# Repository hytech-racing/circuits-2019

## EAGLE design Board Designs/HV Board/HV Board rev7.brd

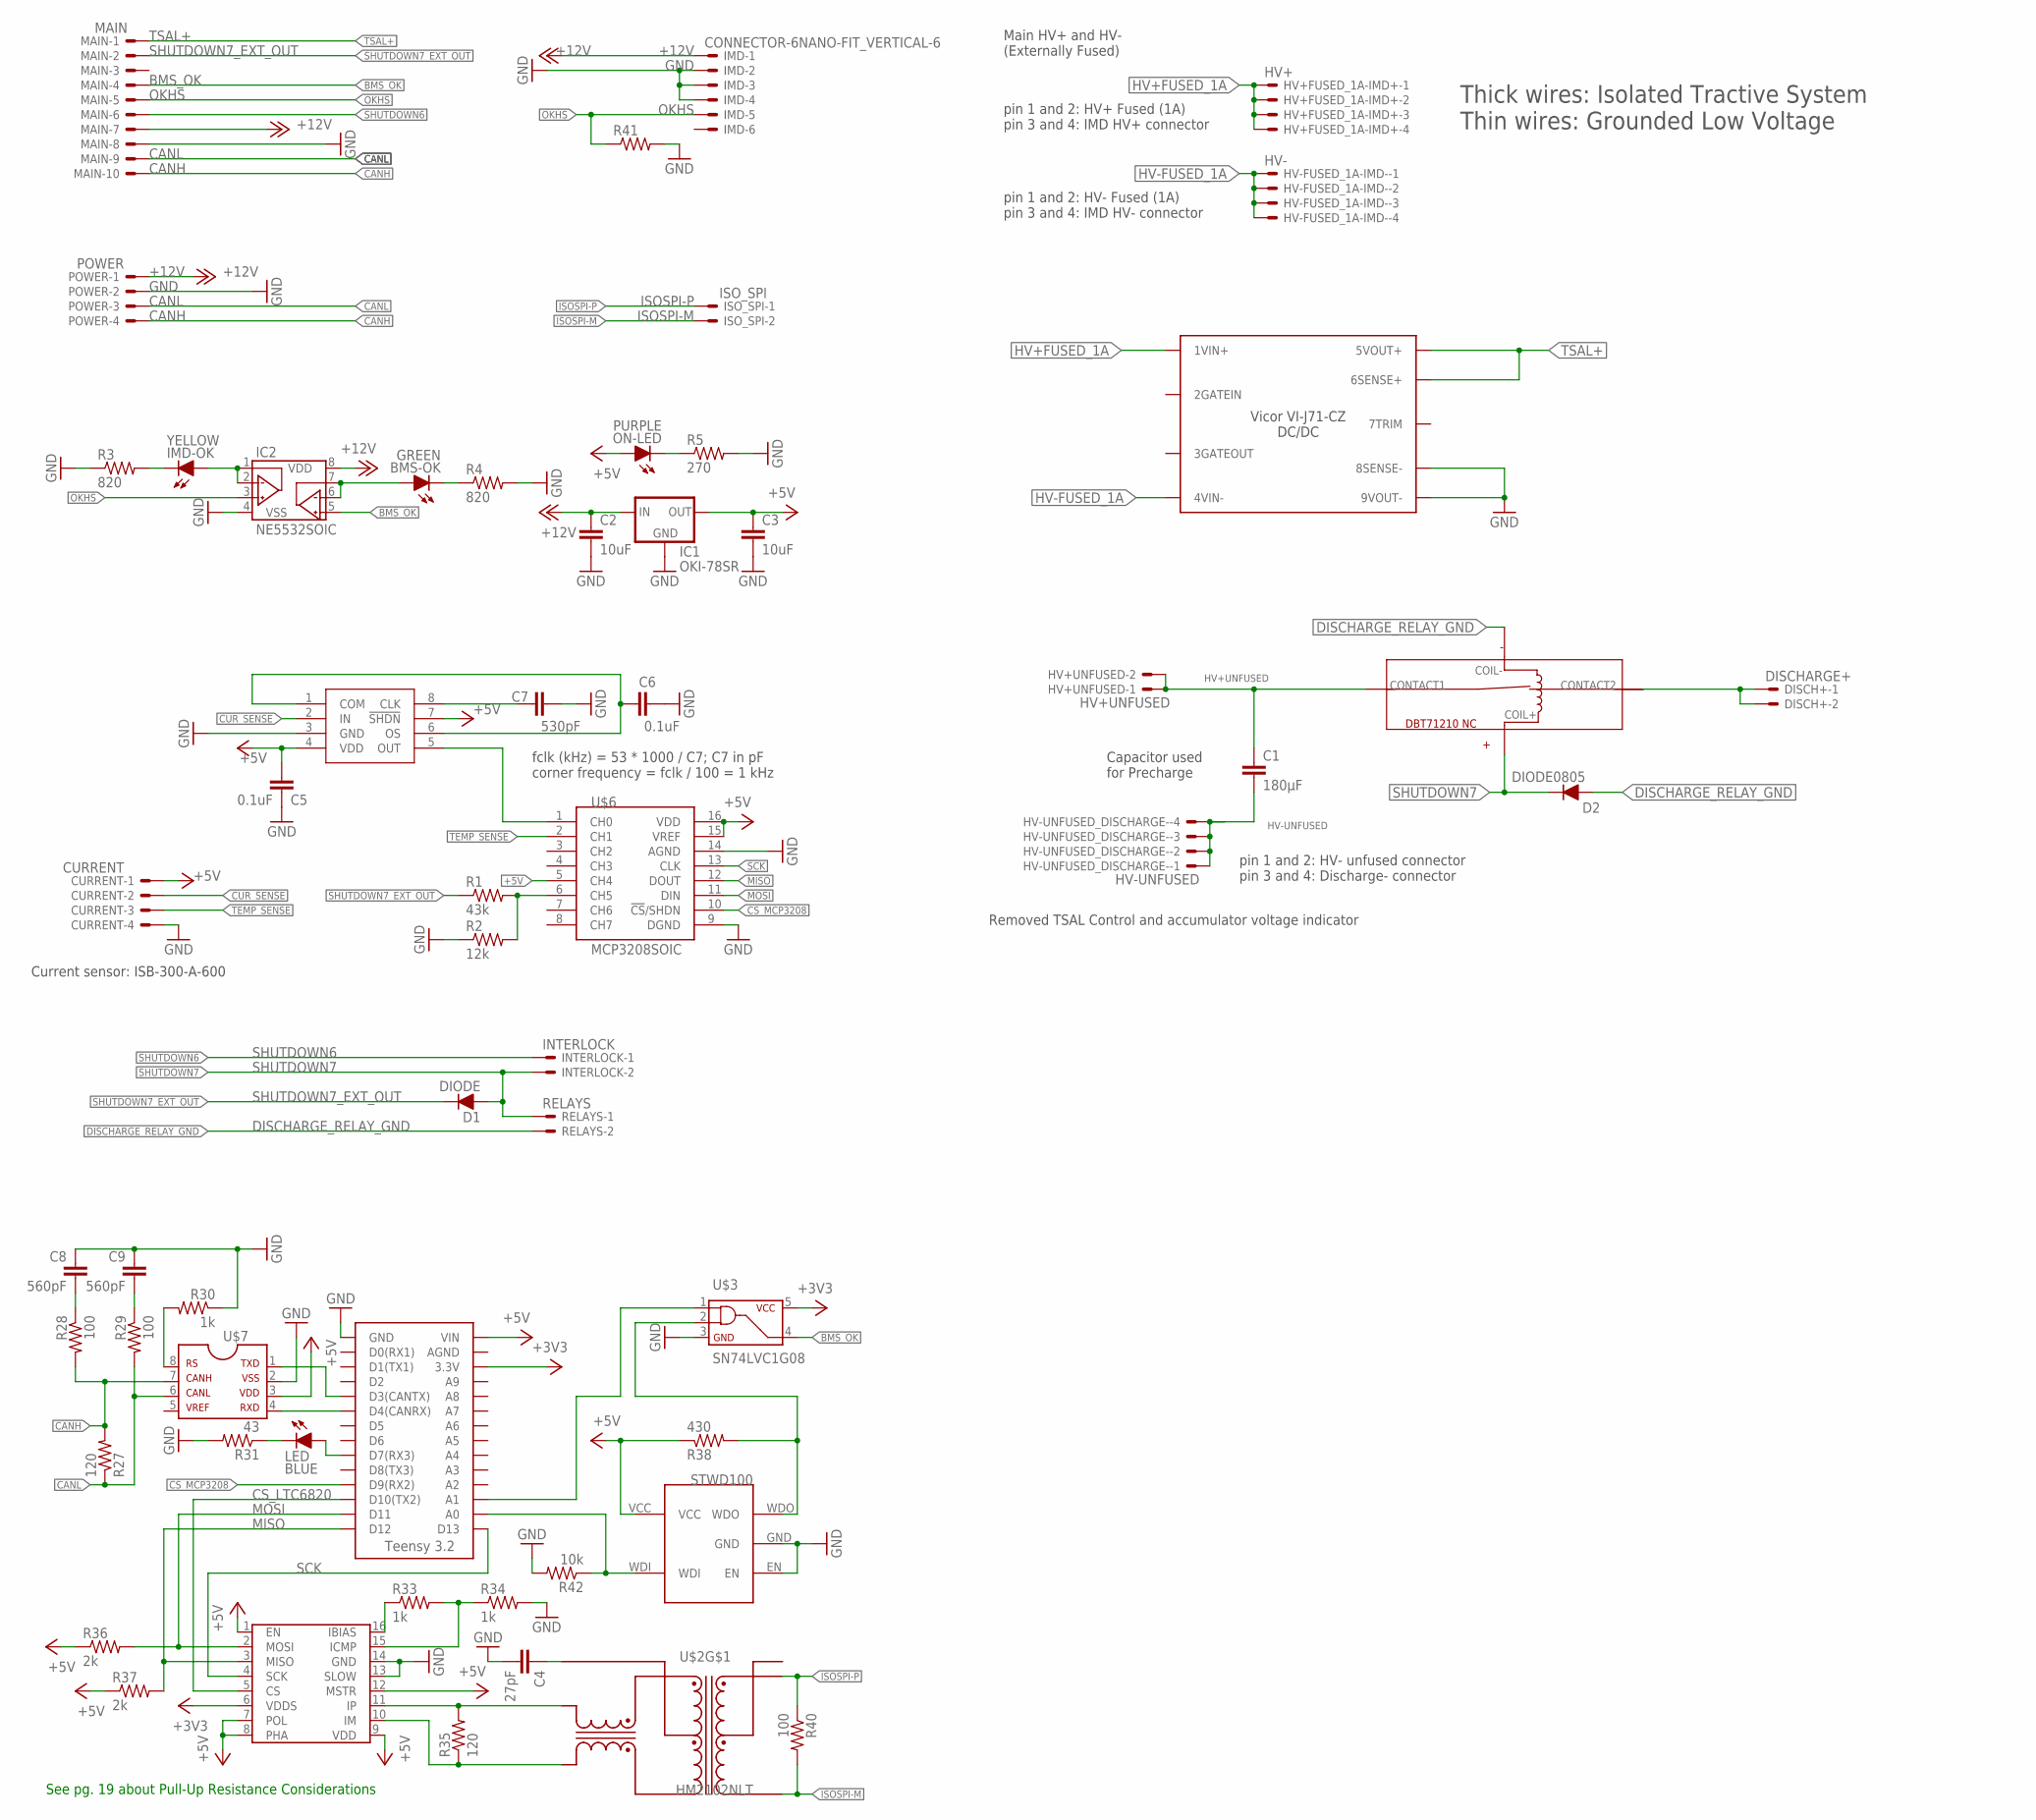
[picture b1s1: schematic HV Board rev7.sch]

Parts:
BMS-OK: GREEN; LED-805
C1: 180µF; LLS2V221MELZ
C2, C3: 10uF; 0805
C4: 27pF; 0805
C5, C6: 0.1uF; 0805
C7: 530pF; 0805
C8, C9: 560pF; 0805
CURRENT: CURRENT; NANO-FIT_VERTICAL-4
D1: DIODE; DO-41
D2: DIODE0805; 0805_D
DISCH+: DISCHARGE+; NANO-FIT_VERTICAL-2
HV+FUSED_1A-IMD+: HV+; NANO-FIT_VERTICAL-4
HV+UNFUSED: HV+UNFUSED; NANO-FIT_VERTICAL-2
HV-FUSED_1A-IMD-: HV-; NANO-FIT_VERTICAL-4
HV-UNFUSED_DISCHARGE-: HV-UNFUSED; NANO-FIT_VERTICAL-4
IC1: OKI-78SR
IC2: NE5532SOIC; SOIC-08
IMD: CONNECTOR-6NANO-FIT_VERTICAL-6; NANO-FIT_VERTICAL-6
IMD-OK: YELLOW; LED-805
INTERLOCK: INTERLOCK; NANO-FIT_VERTICAL-2
ISO_SPI: ISO_SPI; NANO-FIT_VERTICAL-2
LED: BLUE; LED-805
MAIN: MAIN; NANO-FIT_VERTICAL-10
ON-LED: PURPLE; LED-805
POWER: POWER; NANO-FIT_VERTICAL-4
R1: 43k; 0805
R2: 12k; 0805
R3, R4: 820; 0805
R5: 270; 0805
R27, R35: 120; 0805
R28, R29, R40: 100; 0805
R30, R33, R34: 1k; 0805
R31: 43; 0805
R36, R37, R41: 2k; 0805
R38: 430; 0805
R42: 10k; 0805
RELAYS: RELAYS; NANO-FIT_VERTICAL-2
U$1: MAX7480; SOIC-08
U$2: HM2102NLT
U$3: SN74LVC1G08; SOT-23-5
U$4: DBT71210
U$5: HV_DCDC_VI-J71-CZ
U$6: MCP3208SOIC; SOIC-16
U$7: MCP2551; SOIC-08
U$8: LTC6820; MSOP-16
U$9: TEENSY_3.2_SIMPLE
U$10: STWD100; SOT23-5

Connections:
+3V3: U$3.5, U$8.6 (VDDS), U$9.3.3V
+5V: C3.1, C5.1, CURRENT.P$1, IC1.3 (OUT), ON-LED.A, R36.1, R37.1, R38.1, U$1.4 (VDD), U$1.7 (!SHDN), U$6.5 (CH4), U$6.15 (VREF), U$6.16 (VDD), U$7.3, U$8.1 (EN), U$8.7 (POL), U$8.8 (PHA), U$8.9 (VDD), U$8.12 (MSTR), U$9.VIN, U$10.VCC
+12V: C2.1, IC1.1 (IN), IC2.8 (VDD), IMD.P$1, MAIN.P$7, POWER.P$1
BMS_OK: IC2.5 (VINB+), MAIN.P$4, U$3.4
CANH: MAIN.P$10, POWER.P$4, R27.2, R28.2, U$7.7
CANL: MAIN.P$9, POWER.P$3, R27.1, R29.2, U$7.6
CS_LTC6820: U$8.5 (CS), U$9.D10(TX2)
CS_MCP3208: U$6.10 (!CS!/SHDN), U$9.D9(RX2)
CUR_SENSE: CURRENT.P$2, U$1.2 (IN)
DISCHARGE_RELAY_GND: D2.A, RELAYS.P$2, U$4.COIL-
GND: C2.2, C3.2, C4.2, C5.2, C6.2, C7.2, C8.1, C9.1, CURRENT.P$4, IC1.2 (GND), IC2.4 (VSS), IMD.P$2, IMD.P$3, IMD.P$4, MAIN.P$8, POWER.P$2, R2.1, R3.1, R4.2, R5.2, R30.1, R31.2, R34.2, R41.2, R42.2, U$1.3 (GND), U$3.3, U$5.8SENSE-, U$5.9VOUT-, U$6.9 (DGND), U$6.14 (AGND), U$7.2, U$8.13 (SLOW), U$8.14 (GND), U$9.GND, U$10.EN, U$10.GND
HV+FUSED_1A: HV+FUSED_1A-IMD+.P$1, HV+FUSED_1A-IMD+.P$2, HV+FUSED_1A-IMD+.P$3, HV+FUSED_1A-IMD+.P$4, U$5.1VIN+
HV+UNFUSED: C1.P$1 (1), HV+UNFUSED.P$1, HV+UNFUSED.P$2, U$4.CONTACT1
HV+UNFUSED_FSAE_DISCHARGE: DISCH+.P$1, DISCH+.P$2, U$4.CONTACT2
HV-FUSED_1A: HV-FUSED_1A-IMD-.P$1, HV-FUSED_1A-IMD-.P$2, HV-FUSED_1A-IMD-.P$3, HV-FUSED_1A-IMD-.P$4, U$5.4VIN-
HV-UNFUSED: C1.P$2 (2), HV-UNFUSED_DISCHARGE-.P$1, HV-UNFUSED_DISCHARGE-.P$2, HV-UNFUSED_DISCHARGE-.P$3, HV-UNFUSED_DISCHARGE-.P$4
IM: R35.1, U$2.P$10 (TD-), U$8.10 (IM)
IP: R35.2, U$2.P$12 (TD+), U$8.11 (IP)
ISOSPI-M: ISO_SPI.P$2, R40.2, U$2.P$3 (MX-)
ISOSPI-P: ISO_SPI.P$1, R40.1, U$2.P$1 (MX+)
MISO: R37.2, U$6.12 (DOUT), U$8.3 (MISO), U$9.D12
MOSI: R36.2, U$6.11 (DIN), U$8.2 (MOSI), U$9.D11
unnamed: U$1.5 (OUT), U$6.1 (CH0)
unnamed: C6.1, U$1.1 (COM), U$1.6 (OS)
unnamed: ON-LED.C, R5.1
unnamed: C7.1, U$1.8 (CLK)
unnamed: R1.2, R2.2, U$6.6 (CH5)
unnamed: U$7.1, U$9.D3(CANTX)
unnamed: R30.2, U$7.8
unnamed: C8.2, R28.1
unnamed: C9.2, R29.1
unnamed: LED.C, R31.1
unnamed: R33.1, U$8.16 (IBIAS)
unnamed: R33.2, R34.1, U$8.15 (ICMP)
unnamed: C4.1, U$2.P$11 (TCT)
unnamed: U$7.4, U$9.D4(CANRX)
unnamed: LED.A, U$9.D7(RX3)
unnamed: R38.2, U$3.2, U$10.WDO
unnamed: U$3.1, U$9.A1
unnamed: IC2.1 (VOUTA), IC2.2 (VINA-), IMD-OK.A
unnamed: BMS-OK.A, IC2.6 (VINB-), IC2.7 (VOUTB)
unnamed: BMS-OK.C, R4.1
unnamed: IMD-OK.C, R3.2
unnamed: R42.1, U$9.A0, U$10.WDI
OKHS: IC2.3 (VINA+), IMD.P$5, MAIN.P$5, R41.1
SCK: U$6.13 (CLK), U$8.4 (SCK), U$9.D13
SHUTDOWN6: INTERLOCK.P$1, MAIN.P$6
SHUTDOWN7: D1.A, D2.C, INTERLOCK.P$2, RELAYS.P$1, U$4.COIL+
SHUTDOWN7_EXT_OUT: D1.C, MAIN.P$2, R1.1
TEMP_SENSE: CURRENT.P$3, U$6.2 (CH1)
TSAL+: MAIN.P$1, U$5.5VOUT+, U$5.6SENSE+

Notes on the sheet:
Current sensor: ISB-300-A-600
Main HV+ and HV- (Externally Fused)
Thick wires: Isolated Tractive System Thin wires: Grounded Low Voltage
See pg. 19 about Pull-Up Resistance Considerations
Capacitor used for Precharge
Removed TSAL Control and accumulator voltage indicator
pin 1 and 2: HV+ Fused (1A) pin 3 and 4: IMD HV+ connector
pin 1 and 2: HV- Fused (1A) pin 3 and 4: IMD HV- connector
pin 1 and 2: HV- unfused connector pin 3 and 4: Discharge- connector
fclk (kHz) = 53 * 1000 / C7; C7 in pF corner frequency = fclk / 100 = 1 kHz

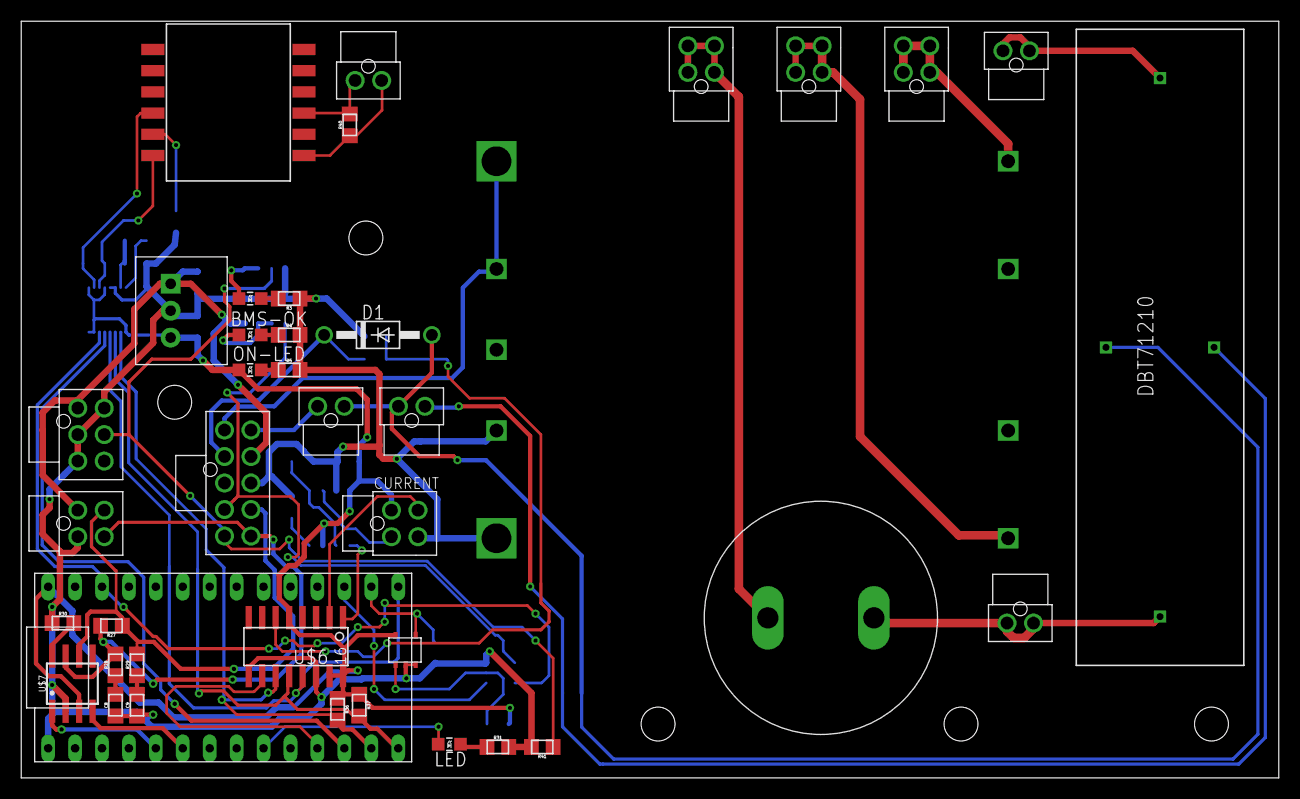
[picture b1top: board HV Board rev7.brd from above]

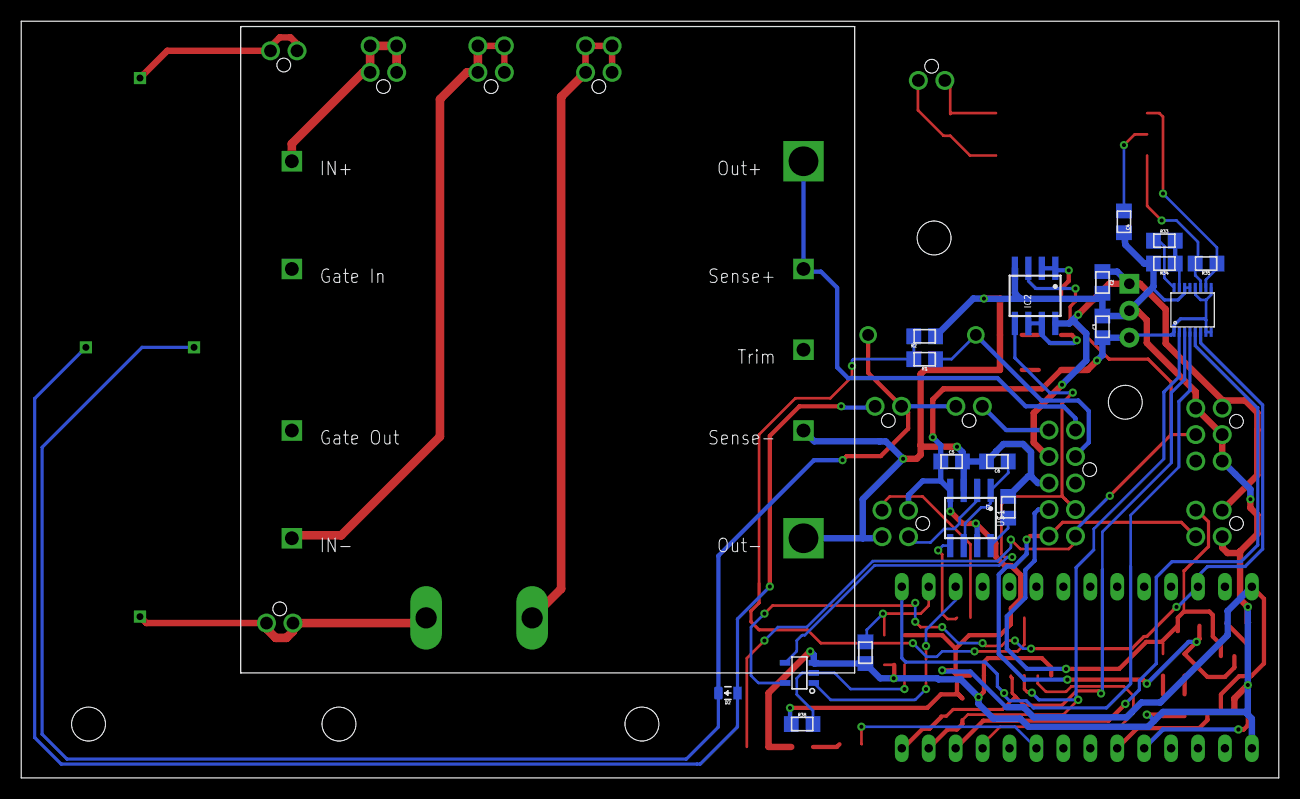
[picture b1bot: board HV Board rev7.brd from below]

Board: 2 copper layers, 118.6 x 71.4 mm, 58 parts (19 on the bottom side), 51 nets.

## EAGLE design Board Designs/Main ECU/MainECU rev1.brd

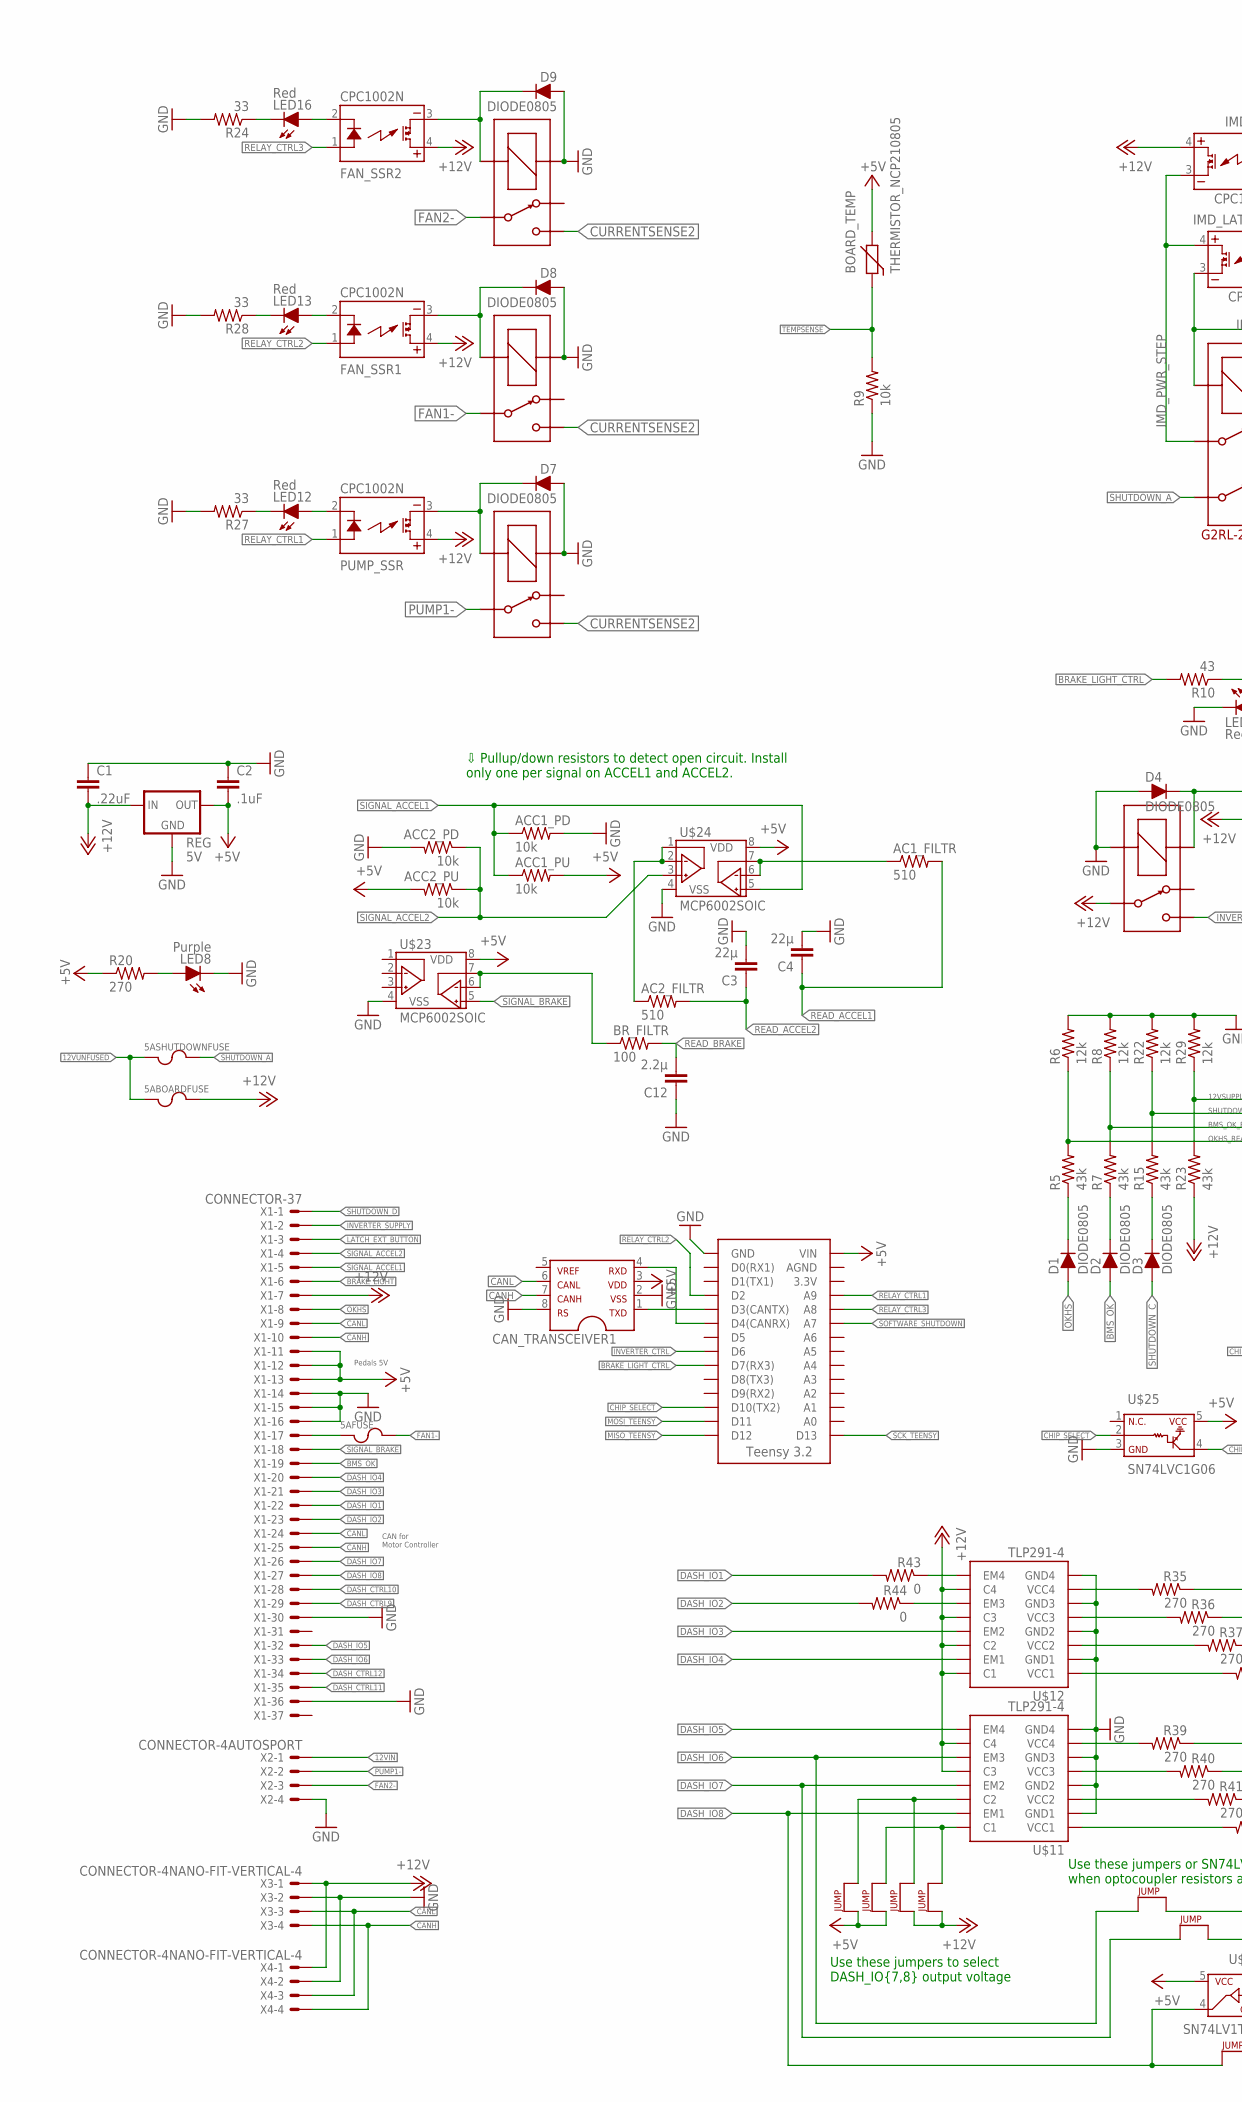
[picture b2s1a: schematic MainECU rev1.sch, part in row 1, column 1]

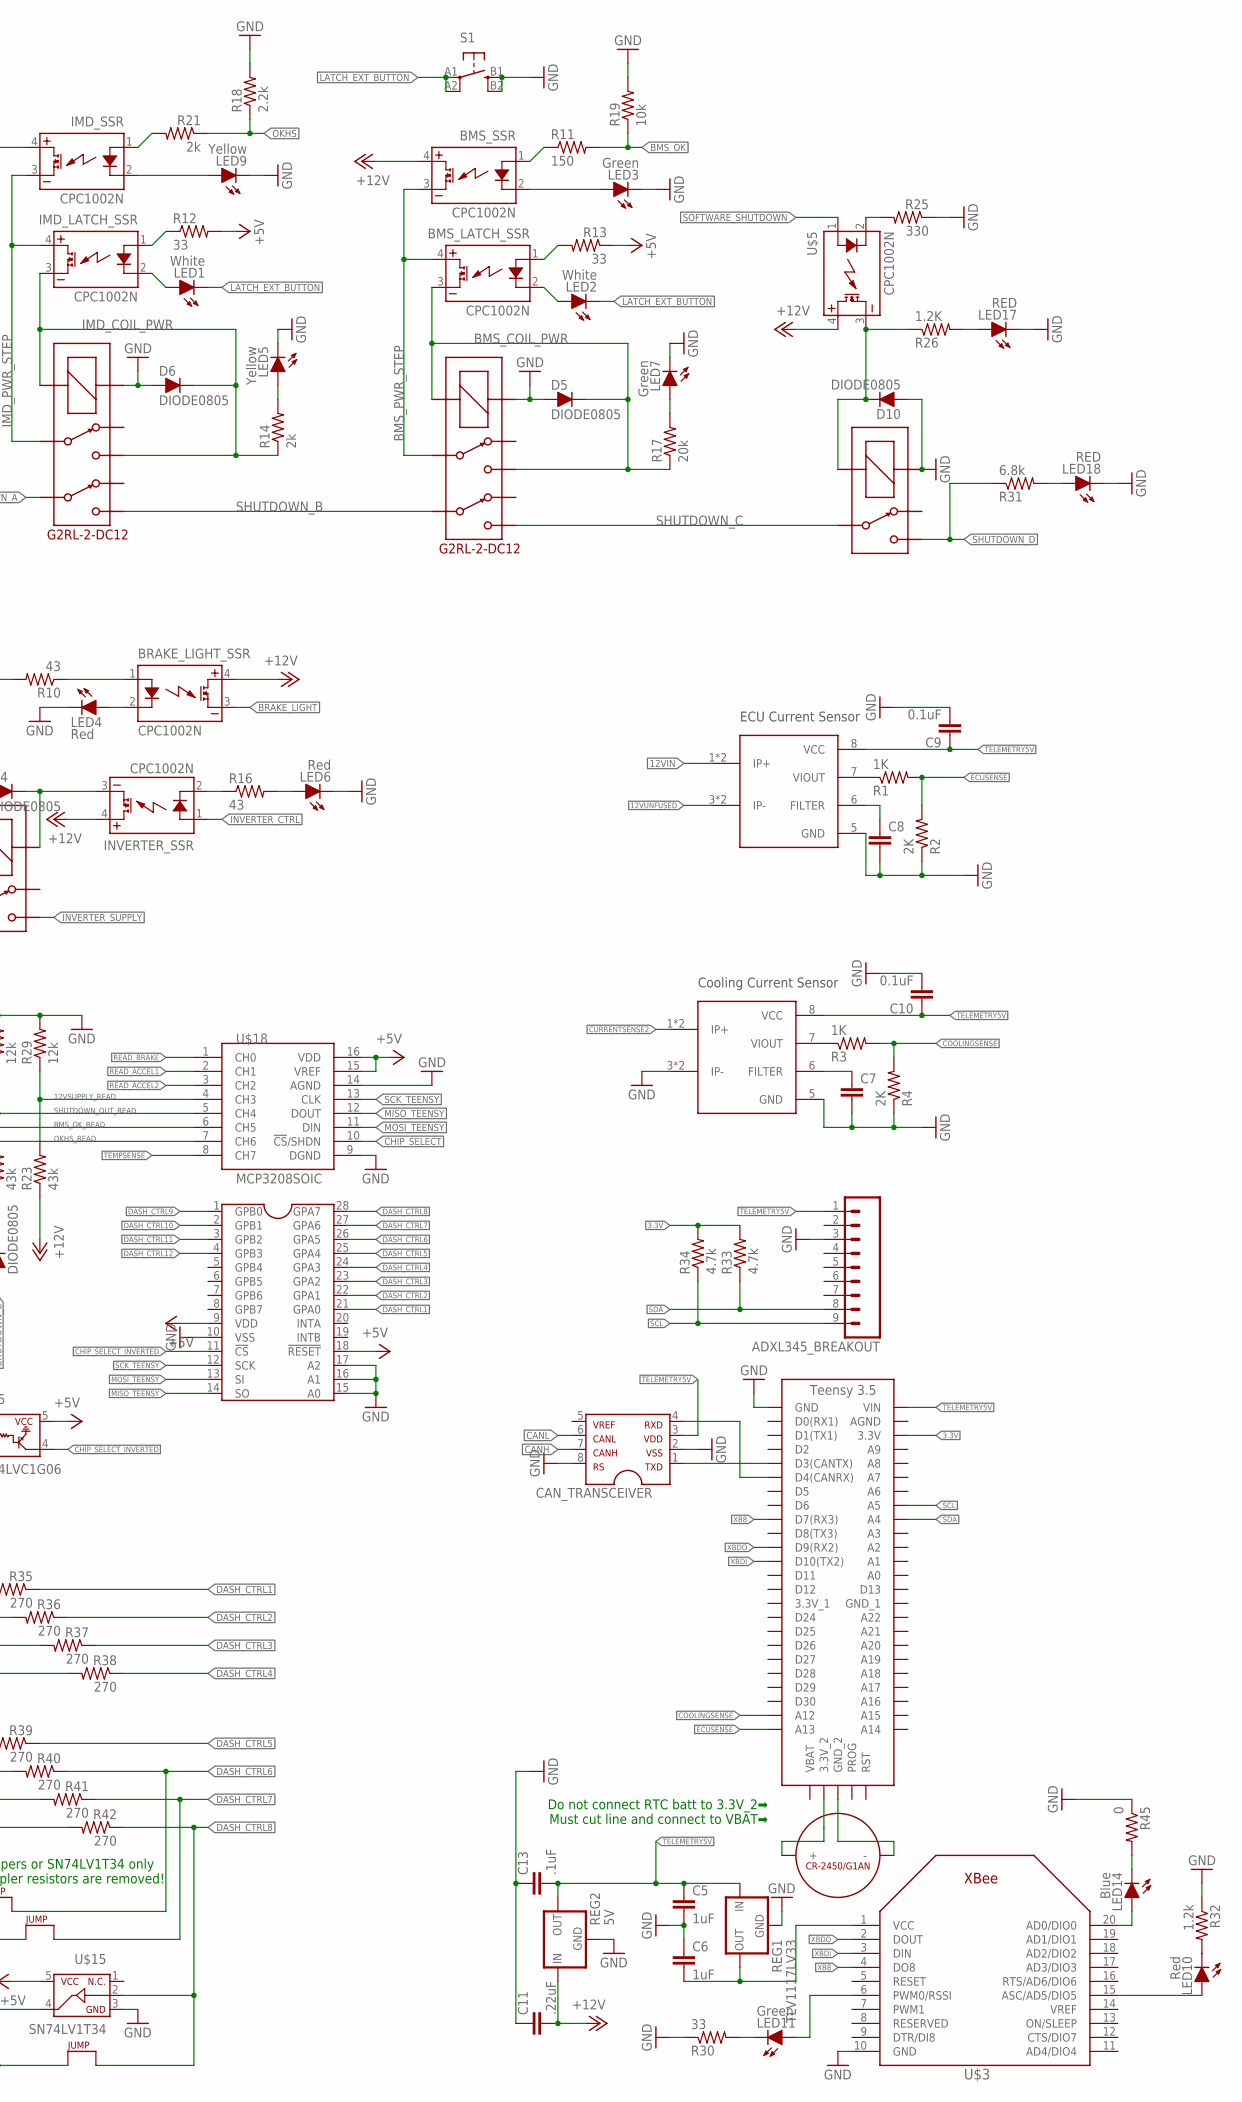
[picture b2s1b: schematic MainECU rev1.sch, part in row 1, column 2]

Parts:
5ABOARDFUSE, 5AFUSE, 5ASHUTDOWNFUSE: FUSE_MINIBLADE; MINI-BLADE_FUSE_HOLDER
AC1_FILTR, AC2_FILTR: 510; 0805
ACC1_PD, ACC1_PU, ACC2_PD, ACC2_PU: 10k; 0805
ADXL345_BREAKOUT: M09; 1X09
BMS_LATCH_SSR: CPC1002N; SOP04
BMS_SSR: CPC1002N; SOP04
BOARD_TEMP: THERMISTOR_NCP210805; 0805
BRAKE_LIGHT_SSR: CPC1002N; SOP04
BR_FILTR: 100; 0805
C1, C11: .22uF; 0805
C2, C13: .1uF; 0805
C3, C4: 22µ; 0805
C5, C6: 1uF; 0805
C7, C8: CAP0805; 0805
C9, C10: 0.1uF; 0805
C12: 2.2µ; 0805
CAN_TRANSCEIVER, CAN_TRANSCEIVER1: MCP2551; SOIC-08
D1, D2, D3, D4, D5, D6, D7, D8, D9, D10: DIODE0805; 0805_D
FAN_SSR1, FAN_SSR2: CPC1002N; SOP04
IMD_LATCH_SSR: CPC1002N; SOP04
IMD_SHUTDOWN, IMD_SHUTDOWN1: G2RL-2-DC12; G2RL-2
IMD_SSR: CPC1002N; SOP04
INVERTER_SSR: CPC1002N; SOP04
LED1, LED2: White; LED-805
LED3, LED7, LED11: Green; LED-805
LED4, LED6, LED10, LED12, LED13, LED16: Red; LED-805
LED5, LED9: Yellow; LED-805
LED8: Purple; LED-805
LED14: Blue; LED-805
LED17, LED18: RED; LED-805
PUMP_SSR: CPC1002N; SOP04
R1, R3: 1K; 0805
R2, R4: 2K; 0805
R5, R7, R15, R23: 43k; 0805
R6, R8, R22, R29: 12k; 0805
R9, R19: 10k; 0805
R10, R16: 43; 0805
R11: 150; 0805
R12, R13, R24, R27, R28, R30: 33; 0805
R14, R21: 2k; 0805
R17: 20k; 0805
R18: 2.2k; 0805
R20, R35, R36, R37, R38, R39, R40, R41, R42: 270; 0805
R25: 330; 0805
R26: 1.2K; 0805
R31: 6.8k; 0805
R32: 1.2k; 0805
R33, R34: 4.7k; 0805
R43, R44, R45: 0; 0805
REG, REG2: 5V; OKI-78SR
REG1: TLV1117LV33; SOT223
S1: BTN_10-XXSMD; TACTILE_SWITCH_SMD_6.2MM_TALL
SOFTWARE_SHUTOFF: G5LE; ZF112
U$1: TEENSY_3.2_SIMPLE
U$2: TEENSY_3.5_EXT
U$3: XBEE
U$4, U$6, U$7, U$8: G5LE; ZF112
U$5: CPC1002N; SOP04
U$9, U$10: ACS715_CURRENT_SENSOR; SOP8
U$11, U$12: TLP291-4; SOIC-16
U$13, U$14, U$16, U$19, U$20, U$21, U$22: JUMPER; 0805
U$15: SN74LV1T34; SOT-23-5
U$17: MCP23S17SSOP28; SSOP28
U$18: MCP3208SOIC; SOIC-16
U$23, U$24: MCP6002SOIC; SOIC-08
U$25: SN74LVC1G06; SOT-23-5
U$26: CR-2450/G1AN
X1: CONNECTOR-37; AUTOSPORT_14-35
X2: CONNECTOR-4AUTOSPORT; AUTOSPORT_12-04
X3, X4: CONNECTOR-4NANO-FIT-VERTICAL-4; NANO-FIT_VERTICAL-4

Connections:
3.3V: R33.2, R34.2, U$2.3.3V
12VIN: U$9.1 (IP+), U$9.2 (IP+), X2.P$1
12VSUPPLY_READ: R23.2, R29.1, U$18.4 (CH3)
12VUNFUSED: 5ABOARDFUSE.L1 (1), 5ABOARDFUSE.L2 (1), 5ASHUTDOWNFUSE.L1 (1), 5ASHUTDOWNFUSE.L2 (1), U$9.3 (IP-), U$9.4 (IP-)
+5V: ACC1_PU.2, ACC2_PU.2, BOARD_TEMP.1, C2.2, CAN_TRANSCEIVER1.3, R12.2, R13.1, R20.1, REG.3 (OUT), U$1.VIN, U$15.5, U$17.9 (VDD), U$17.18 (!RESET), U$18.15 (VREF), U$18.16 (VDD), U$20.1, U$22.1, U$23.8 (VDD), U$24.8 (VDD), U$25.5, X1.P$11, X1.P$12, X1.P$13
+12V: 5ABOARDFUSE.R1 (2), 5ABOARDFUSE.R2 (2), BMS_SSR.4 (DC+), BRAKE_LIGHT_SSR.4 (DC+), C1.2, C11.2, FAN_SSR1.4 (DC+), FAN_SSR2.4 (DC+), IMD_SSR.4 (DC+), INVERTER_SSR.4 (DC+), PUMP_SSR.4 (DC+), R23.1, REG.1 (IN), REG2.1 (IN), U$5.4 (DC+), U$8.P, U$11.10 (C4), U$11.12 (C3), U$12.10 (C4), U$12.12 (C3), U$12.14 (C2), U$12.16 (C1), U$16.1, U$21.1, X1.P$7, X3.P$1, X4.P$1
BMS_COIL_PWR: BMS_LATCH_SSR.3 (DC-), D5.C, IMD_SHUTDOWN1.4, IMD_SHUTDOWN1.COIL-, R17.1
BMS_OK: D2.A, R11.2, R19.1, X1.P$19
BMS_OK_READ: R7.2, R8.1, U$18.6 (CH5)
BMS_PWR_STEP: BMS_LATCH_SSR.4 (DC+), BMS_SSR.3 (DC-), IMD_SHUTDOWN1.3
BRAKE_LIGHT: BRAKE_LIGHT_SSR.3 (DC-), X1.P$6
BRAKE_LIGHT_CTRL: R10.2, U$1.D7(RX3)
CANH: CAN_TRANSCEIVER.7, CAN_TRANSCEIVER1.7, X1.P$10, X1.P$25, X3.P$4, X4.P$4
CANL: CAN_TRANSCEIVER.6, CAN_TRANSCEIVER1.6, X1.P$9, X1.P$24, X3.P$3, X4.P$3
CHIP_SELECT: U$1.D10(TX2), U$18.10 (!CS!/SHDN), U$25.2
CHIP_SELECT_INVERTED: U$17.11 (!CS), U$25.4
COOLINGSENSE: R3.2, R4.2, U$2.A12
CURRENTSENSE2: U$4.S, U$6.S, U$7.S, U$10.1 (IP+), U$10.2 (IP+)
DASH_CTRL1: R35.1, U$17.21 (GPA0)
DASH_CTRL2: R36.1, U$17.22 (GPA1)
DASH_CTRL3: R37.1, U$17.23 (GPA2)
DASH_CTRL4: R38.1, U$17.24 (GPA3)
DASH_CTRL5: R39.1, U$17.25 (GPA4)
DASH_CTRL6: R40.1, U$13.2, U$17.26 (GPA5)
DASH_CTRL7: R41.1, U$14.2, U$17.27 (GPA6)
DASH_CTRL8: R42.1, U$15.2, U$17.28 (GPA7), U$19.2
DASH_CTRL9: U$17.1 (GPB0), X1.P$29
DASH_CTRL10: U$17.2 (GPB1), X1.P$28
DASH_CTRL11: U$17.3 (GPB2), X1.P$35
DASH_CTRL12: U$17.4 (GPB3), X1.P$34
DASH_IO1: R43.2, X1.P$22
DASH_IO2: R44.2, X1.P$23
DASH_IO3: U$12.13 (EM2), X1.P$21
DASH_IO4: U$12.15 (EM1), X1.P$20
DASH_IO5: U$11.9 (EM4), X1.P$32
DASH_IO6: U$11.11 (EM3), U$13.1, X1.P$33
DASH_IO7: U$11.13 (EM2), U$14.1, X1.P$26
DASH_IO8: U$11.15 (EM1), U$15.4, U$19.1, X1.P$27
ECUSENSE: R1.2, R2.2, U$2.A13
FAN1-: 5AFUSE.R1 (2), 5AFUSE.R2 (2), U$7.P
FAN2-: U$4.P, X2.P$3
GND: ACC1_PD.2, ACC2_PD.2, ADXL345_BREAKOUT.3, C1.1, C2.1, C3.2, C4.2, C5.2, C6.1, C7.2, C8.2, C9.2, C10.2, C11.1, C12.1, C13.1, CAN_TRANSCEIVER.2, CAN_TRANSCEIVER.8, CAN_TRANSCEIVER1.2, CAN_TRANSCEIVER1.8, D4.A, D5.A, D6.A, D7.A, D8.A, D9.A, D10.A, IMD_SHUTDOWN.COIL+, IMD_SHUTDOWN1.COIL+, LED3.C, LED4.C, LED5.C, LED6.C, LED7.C, LED8.C, LED9.C, LED17.C, LED18.C, R2.1, R4.1, R6.2, R8.2, R9.1, R18.2, R19.2, R22.2, R24.2, R25.1, R27.2, R28.2, R29.2, R30.1, R32.1, R45.1, REG.2 (GND), REG1.1 (GND), REG2.2 (GND), S1.B1 (S), S1.B2 (S1), SOFTWARE_SHUTOFF.1 (COIL+), U$1.GND, U$2.GND, U$3.10 (GND), U$4.1 (COIL+), U$6.1 (COIL+), U$7.1 (COIL+), U$8.2 (COIL-), U$9.5 (GND), U$10.3 (IP-), U$10.4 (IP-), U$10.5 (GND), U$11.2 (GND1), U$11.4 (GND2), U$11.6 (GND3), U$11.8 (GND4), U$12.2 (GND1), U$12.4 (GND2), U$12.6 (GND3), U$12.8 (GND4), U$15.3, U$17.10 (VSS), U$17.15 (A0), U$17.16 (A1), U$17.17 (A2), U$18.9 (DGND), U$18.14 (AGND), U$23.4 (VSS), U$24.4 (VSS), U$25.3, X1.P$14, X1.P$15, X1.P$16, X1.P$30, X1.P$36, X2.P$4, X3.P$2, X4.P$2
IMD_COIL_PWR: D6.C, IMD_LATCH_SSR.3 (DC-), IMD_SHUTDOWN.4, IMD_SHUTDOWN.COIL-, R14.1
IMD_PWR_STEP: IMD_LATCH_SSR.4 (DC+), IMD_SHUTDOWN.3, IMD_SSR.3 (DC-)
INVERTER_CTRL: INVERTER_SSR.1 (CONTROL+), U$1.D6
INVERTER_SUPPLY: U$8.S, X1.P$2
LATCH_EXT_BUTTON: LED1.C, LED2.C, S1.A1, S1.A2 (P1), X1.P$3
MISO_TEENSY: U$1.D12, U$17.14 (SO), U$18.12 (DOUT)
MOSI_TEENSY: U$1.D11, U$17.13 (SI), U$18.11 (DIN)
unnamed: 5AFUSE.L1 (1), 5AFUSE.L2 (1), X1.P$17
unnamed: IMD_LATCH_SSR.2 (CONTROL-), LED1.A
unnamed: R1.1, U$9.7 (VIOUT)
unnamed: D7.C, PUMP_SSR.3 (DC-), U$6.2 (COIL-)
unnamed: IMD_LATCH_SSR.1 (CONTROL+), R12.1
unnamed: R3.1, U$10.7 (VIOUT)
unnamed: BRAKE_LIGHT_SSR.2 (CONTROL-), LED4.A
unnamed: C8.1, U$9.6 (FILTER)
unnamed: BMS_SSR.2 (CONTROL-), LED3.A
unnamed: D1.C, R5.1
unnamed: D2.C, R7.1
unnamed: BMS_LATCH_SSR.1 (CONTROL+), R13.2
unnamed: CAN_TRANSCEIVER.4, U$2.D4(CANRX)
unnamed: CAN_TRANSCEIVER.1, U$2.D3(CANTX)
unnamed: CAN_TRANSCEIVER1.4, U$1.D4(CANRX)
unnamed: BMS_LATCH_SSR.2 (CONTROL-), LED2.A
unnamed: BRAKE_LIGHT_SSR.1 (CONTROL+), R10.1
unnamed: BMS_SSR.1 (CONTROL+), R11.1
unnamed: LED5.A, R14.2
unnamed: D8.C, FAN_SSR1.3 (DC-), U$7.2 (COIL-)
unnamed: D9.C, FAN_SSR2.3 (DC-), U$4.2 (COIL-)
unnamed: CAN_TRANSCEIVER1.1, U$1.D3(CANTX)
unnamed: AC2_FILTR.1, U$24.1 (VOUTA), U$24.2 (VINA-)
unnamed: AC1_FILTR.1, U$24.6 (VINB-), U$24.7 (VOUTB)
unnamed: BR_FILTR.1, U$23.6 (VINB-), U$23.7 (VOUTB)
unnamed: D4.C, INVERTER_SSR.3 (DC-), U$8.1 (COIL+)
unnamed: INVERTER_SSR.2 (CONTROL-), R16.1
unnamed: LED6.A, R16.2
unnamed: LED8.A, R20.2
unnamed: LED16.C, R24.1
unnamed: IMD_SSR.1 (CONTROL+), R21.2
unnamed: LED7.A, R17.2
unnamed: D3.C, R15.1
unnamed: IMD_SSR.2 (CONTROL-), LED9.A
unnamed: LED14.C, R45.2
unnamed: LED13.C, R28.1
unnamed: LED12.C, R27.1
unnamed: LED12.A, PUMP_SSR.2 (CONTROL-)
unnamed: FAN_SSR2.2 (CONTROL-), LED16.A
unnamed: LED18.A, R31.2
unnamed: U$2.3.3V_2, U$26.+_0 (+), U$26.+_1 (+)
unnamed: FAN_SSR1.2 (CONTROL-), LED13.A
unnamed: D10.C, R26.1, SOFTWARE_SHUTOFF.2 (COIL-), U$5.3 (DC-)
unnamed: R25.2, U$5.2 (CONTROL-)
unnamed: LED11.C, R30.2
unnamed: LED17.A, R26.2
unnamed: LED11.A, U$3.6 (PWM0/RSSI)
unnamed: C7.1, U$10.6 (FILTER)
unnamed: LED10.A, U$3.15 (ASC/AD5/DIO5)
unnamed: LED10.C, R32.2
unnamed: R35.2, U$12.7 (VCC4)
unnamed: R36.2, U$12.5 (VCC3)
unnamed: R37.2, U$12.3 (VCC2)
unnamed: R38.2, U$12.1 (VCC1)
unnamed: R39.2, U$11.7 (VCC4)
unnamed: R40.2, U$11.5 (VCC3)
unnamed: R41.2, U$11.3 (VCC2)
unnamed: R42.2, U$11.1 (VCC1)
unnamed: R43.1, U$12.9 (EM4)
unnamed: R44.1, U$12.11 (EM3)
unnamed: U$11.16 (C1), U$16.2, U$20.2
unnamed: U$11.14 (C2), U$21.2, U$22.2
unnamed: LED14.A, U$3.20 (AD0/DIO0)
unnamed: U$2.GND_2, U$26.-
OKHS: D1.A, R18.1, R21.1, X1.P$8
OKHS_READ: R5.2, R6.1, U$18.7 (CH6)
PUMP1-: U$6.P, X2.P$2
READ_ACCEL1: AC1_FILTR.2, C4.1, U$18.2 (CH1)
READ_ACCEL2: AC2_FILTR.2, C3.1, U$18.3 (CH2)
READ_BRAKE: BR_FILTR.2, C12.2, U$18.1 (CH0)
RELAY_CTRL1: PUMP_SSR.1 (CONTROL+), U$1.A9
RELAY_CTRL2: FAN_SSR1.1 (CONTROL+), U$1.D2
RELAY_CTRL3: FAN_SSR2.1 (CONTROL+), U$1.A8
SCK_TEENSY: U$1.D13, U$17.12 (SCK), U$18.13 (CLK)
SCL: ADXL345_BREAKOUT.9, R34.1, U$2.A5
SDA: ADXL345_BREAKOUT.8, R33.1, U$2.A4
SHUTDOWN_A: 5ASHUTDOWNFUSE.R1 (2), 5ASHUTDOWNFUSE.R2 (2), IMD_SHUTDOWN.6
SHUTDOWN_B: IMD_SHUTDOWN.5, IMD_SHUTDOWN1.6
SHUTDOWN_C: D3.A, IMD_SHUTDOWN1.5, SOFTWARE_SHUTOFF.P
SHUTDOWN_D: R31.1, SOFTWARE_SHUTOFF.S, X1.P$1
SHUTDOWN_OUT_READ: R15.2, R22.1, U$18.5 (CH4)
SIGNAL_ACCEL1: ACC1_PD.1, ACC1_PU.1, U$24.5 (VINB+), X1.P$5
SIGNAL_ACCEL2: ACC2_PD.1, ACC2_PU.1, U$24.3 (VINA+), X1.P$4
SIGNAL_BRAKE: U$23.5 (VINB+), X1.P$18
SOFTWARE_SHUTDOWN: U$1.A7, U$5.1 (CONTROL+)
TELEMETRY5V: ADXL345_BREAKOUT.1, C5.1, C9.1, C10.1, C13.2, CAN_TRANSCEIVER.3, REG1.3 (IN), REG2.3 (OUT), U$2.VIN, U$9.8 (VCC), U$10.8 (VCC)
TEMPSENSE: BOARD_TEMP.2, R9.2, U$18.8 (CH7)
VCC: C6.2, REG1.2 (OUT), REG1.4 (OUT), U$3.1 (VCC)
XB8: U$2.D7(RX3), U$3.4 (DO8)
XBDI: U$2.D10(TX2), U$3.3 (DIN)
XBDO: U$2.D9(RX2), U$3.2 (DOUT)

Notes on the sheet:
ECU Current Sensor
Cooling Current Sensor
⇩ Pullup/down resistors to detect open circuit. Install only one per signal on ACCEL1 and ACCEL2.
Use these jumpers or SN74LV1T34 only when optocoupler resistors are removed!
Use these jumpers to select DASH_IO{7,8} output voltage
Pedals 5V
CAN for Motor Controller
Do not connect RTC batt to 3.3V_2➡ Must cut line and connect to VBAT➡

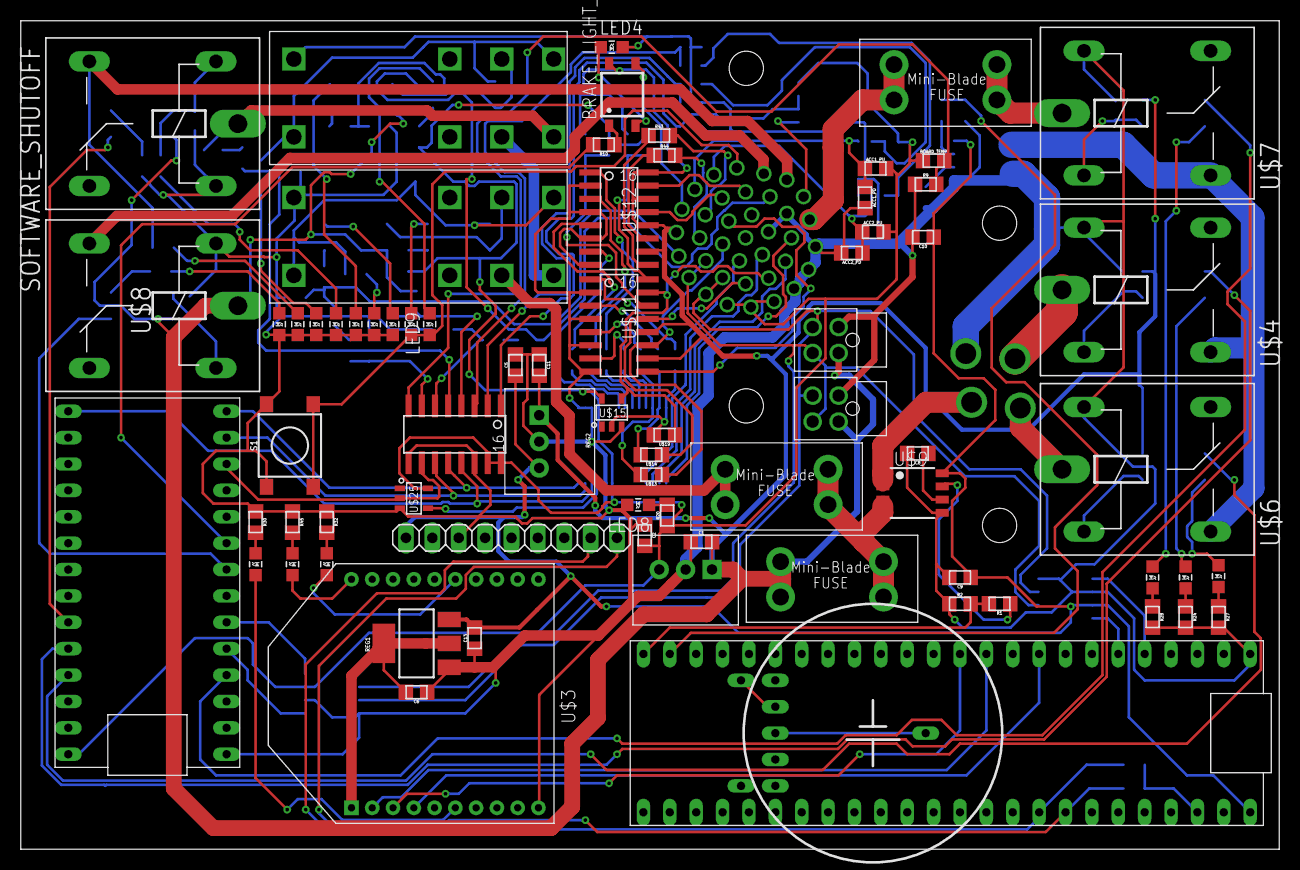
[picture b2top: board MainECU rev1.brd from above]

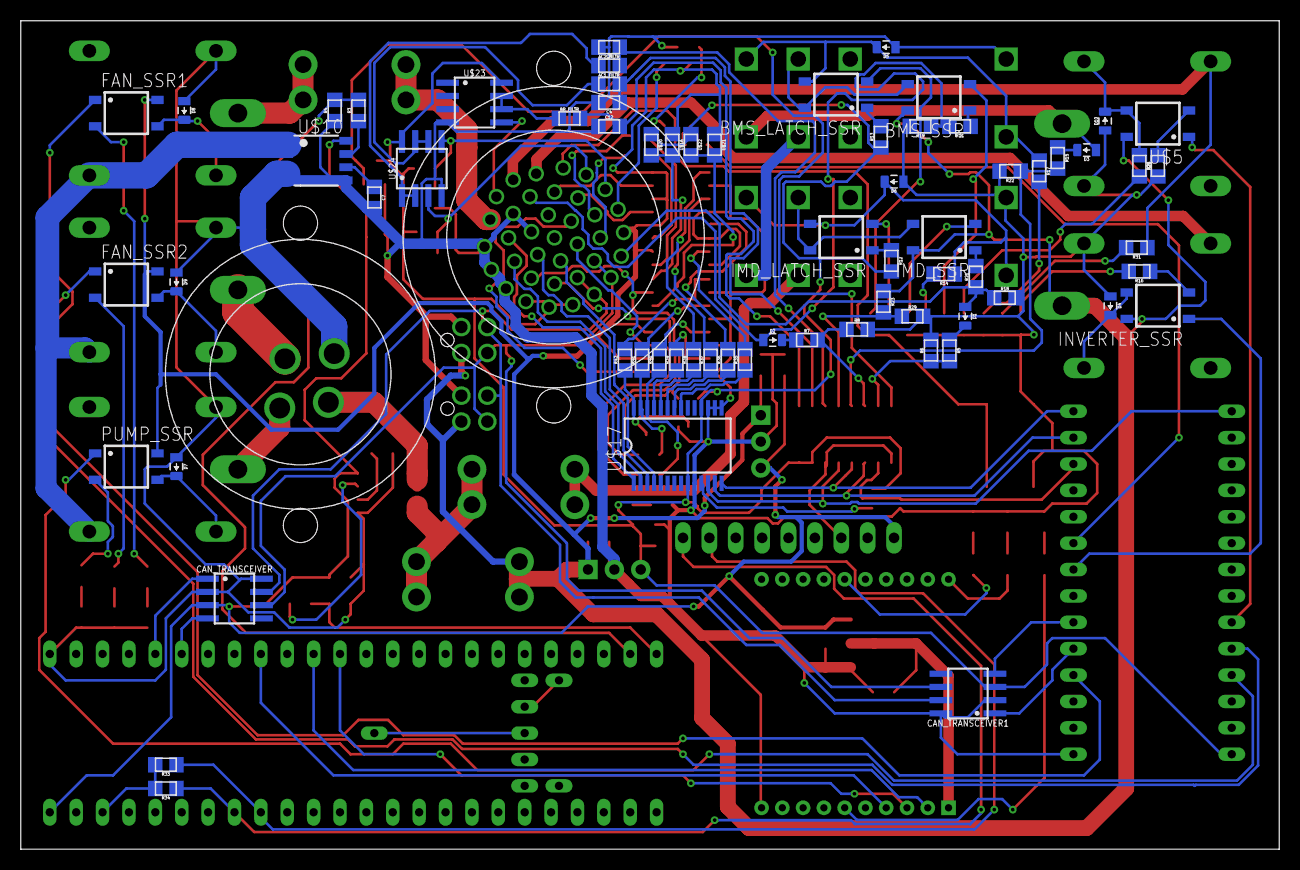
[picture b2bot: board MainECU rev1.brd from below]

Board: 2 copper layers, 121.2 x 79.8 mm, 145 parts (70 on the bottom side), 140 nets.
